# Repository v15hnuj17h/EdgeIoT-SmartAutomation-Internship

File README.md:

# EdgeIoT & Smart Automation Internship

This repository contains my work, notes, code, and documentation from the **10-day EdgeIoT & Smart Automation Internship** conducted by **USIZO Academy**.

Throughout the internship, I explored topics ranging from Git and web deployment to Machine Learning, ESP32 programming, IoT, PCB design, Firebase, and TinyML using Edge Impulse.

---

## Internship Timeline

| Day | Topic | Highlights |
|-----|------|------------|
| **Day 1** | Git & GitHub | Repository creation, version control, documentation using Markdown |
| **Day 2** | Portfolio & Firebase | Built a portfolio website and deployed it using Firebase Hosting |
| **Day 3** | Machine Learning Basics | Introduction to AI, ML pipeline, supervised, unsupervised and reinforcement learning |
| **Day 4** | Development Environment | Installed PlatformIO, ESP32 drivers, Java JDK and required runtimes |
| **Day 5** | Applied Machine Learning | Built a Decision Tree classifier for loan approval prediction using Google Colab |
| **Day 6** | ESP32 Fundamentals | ESP32 architecture, PlatformIO projects, GPIO, Serial communication and PWM |
| **Day 7** | Advanced ESP32 Programming | FreeRTOS, multitasking, timers, GPIO registers, relay control and concurrency |
| **Day 8** | Firebase IoT Dashboard | Controlled an ESP32 remotely using Firebase Realtime Database and a hosted web dashboard |
| **Day 9** | KiCad PCB Design | Designed schematics, PCB layouts, footprints and generated Gerber files |
| **Day 10** | Edge AI & TinyML | Collected MPU6050 motion data, trained an Edge Impulse model and deployed real-time inference on ESP32 |

---

## Repository Structure

```text
.
├── Day-01
├── Day-02
├── Day-03
├── Day-04
├── Day-05
├── Day-06
├── Day-07
├── Day-08
├── Day-09
└── Day-10
```

Each day's folder typically contains:

- `README.md` – Overview of the day's activities
- `notes.md` – Detailed learning notes
- `screenshots/` – Images from practical sessions
- Source code and project files (where applicable)

---

## Technologies & Tools

### Programming
- C++
- Python
- HTML
- CSS
- JavaScript

### Embedded Systems
- ESP32
- MPU6050
- PlatformIO
- Arduino Framework
- FreeRTOS

### IoT & Cloud
- Firebase Hosting
- Firebase Realtime Database

### Machine Learning
- Google Colab
- Scikit-learn
- Decision Trees
- Edge Impulse
- TinyML

### PCB Design
- KiCad

### Version Control
- Git
- GitHub

---

## Skills Gained

- Git and GitHub workflow
- Documentation with Markdown
- Firebase deployment
- Machine Learning fundamentals
- Decision Tree implementation
- ESP32 programming using PlatformIO
- GPIO, PWM and Serial communication
- FreeRTOS multitasking
- Firebase-based IoT applications
- PCB design using KiCad
- Sensor data acquisition
- TinyML model training and deployment
- Real-time inference on ESP32

---

## About

This repository serves as a complete record of my internship journey, documenting both theoretical concepts and practical implementations completed during the program.

It reflects my learning process, hands-on experiments, and projects developed over the course of the internship.

---

**Author:** Vishnujith A

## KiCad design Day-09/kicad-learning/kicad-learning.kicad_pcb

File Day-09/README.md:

# Day 9 - KiCad PCB Design

## Date
26 June 2026

## Objective

Learn the complete PCB design workflow using KiCad, from schematic creation to generating manufacturing files.

## Topics Covered

- Introduction to KiCad
- Schematic Design
- Symbol Libraries
- Footprints
- PCB Layout
- Routing
- Fill Zones
- Silkscreen
- 3D Viewer
- Gerber File Generation

## Activities Performed

- Created a new KiCad project.
- Designed the circuit schematic.
- Assigned footprints to all components.
- Imported the schematic into PCB Editor.
- Placed and routed components.
- Added copper fill zones (Ground Plane).
- Used the silkscreen layer to print text on the PCB.
- Verified the PCB using design rule checks.
- Generated Gerber files.
- Compressed the Gerber files into a ZIP for PCB manufacturing.

## Learning Outcomes

- Learned the complete PCB design workflow.
- Understood the importance of footprints and routing.
- Learned how copper zones improve PCB performance.
- Generated manufacturing-ready Gerber files.

## Summary

Today's session focused on designing a PCB from scratch using KiCad. I completed the full workflow, including schematic design, PCB layout, routing, silkscreen editing, and generating Gerber files for fabrication.

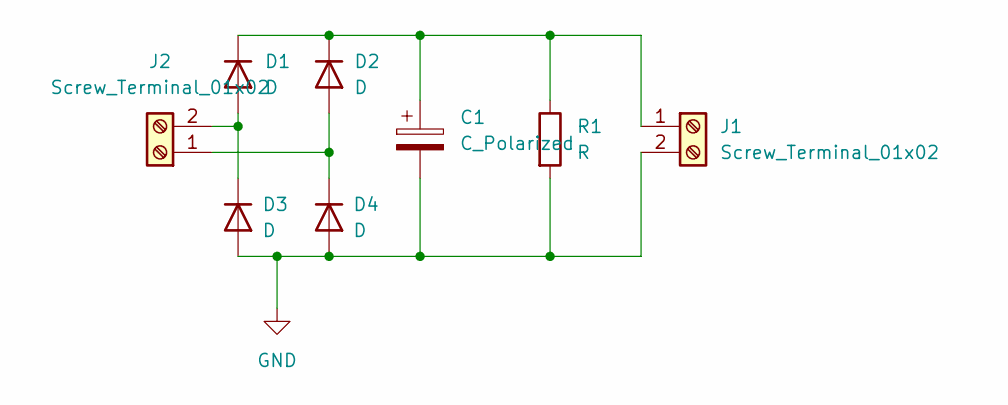
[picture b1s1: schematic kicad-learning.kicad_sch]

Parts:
C1: C_Polarized; CP_Radial_D8.0mm_P5.00mm
D1, D2, D3, D4: D; D_MELF-RM10_Universal_Handsoldering
J1, J2: Screw_Terminal_01x02; TerminalBlock_4Ucon_1x02_P3.50mm_Horizontal
R1: R; R_Axial_DIN0207_L6.3mm_D2.5mm_P7.62mm_Horizontal

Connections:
GND: C1.2, D3.2 (A), D4.2 (A), J1.2, R1.2
unnamed: D1.2 (A), D3.1 (K), J2.2
unnamed: C1.1, D1.1 (K), D2.1 (K), J1.1, R1.1
unnamed: D2.2 (A), D4.1 (K), J2.1

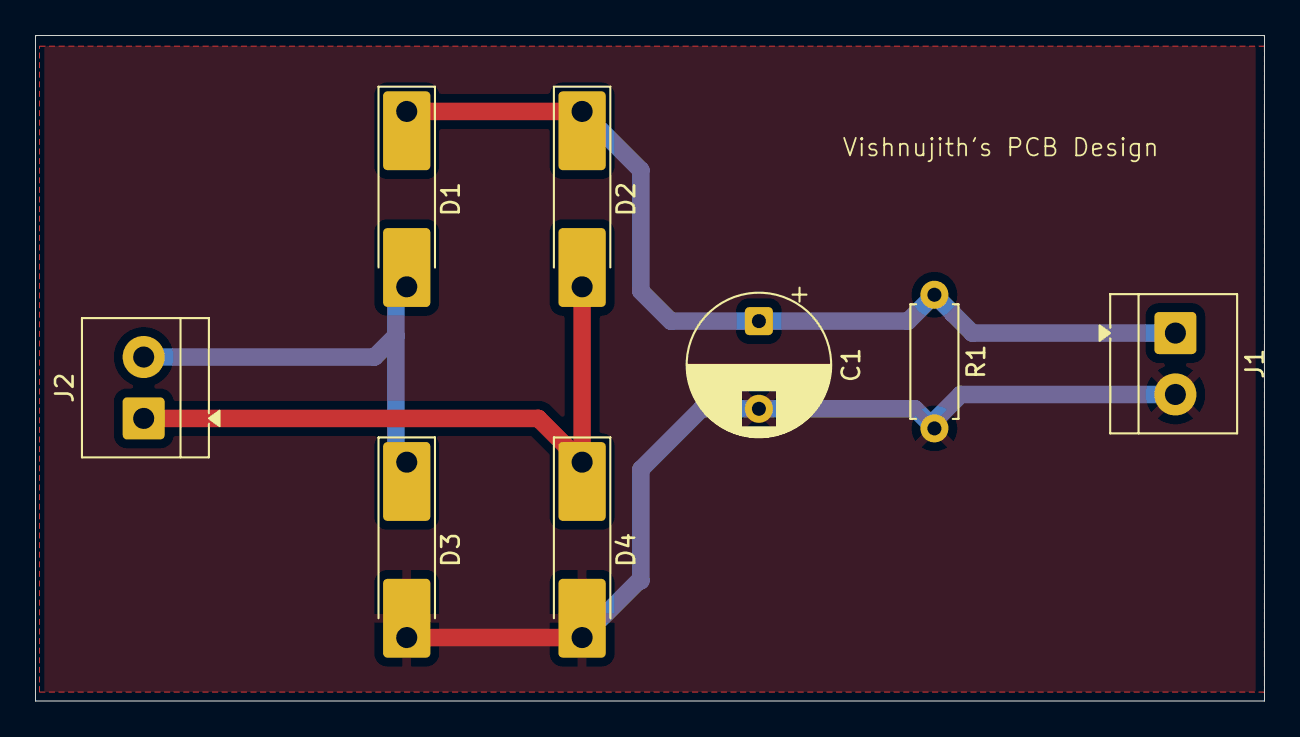
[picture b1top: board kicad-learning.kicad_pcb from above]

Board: 2 copper layers, 70.1 x 37.9 mm, 8 parts (0 on the bottom side), 4 nets.

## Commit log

2026-06-18 Day 1 Done
2026-06-18 Day 1: Git and GitHub
2026-06-19 Day 2: Portfolio Creation and Firebase Deployment
2026-06-20 Day 3: Introduction to ML
2026-06-22 Day 4: Installation & Day 5: Applied ML
2026-06-23 Day 6: Introduction to embedded system
2026-06-24 Day 7: RTOS, LocalHost, etc.
2026-06-26 Day 8: IoT
2026-06-27 Day 9: Kicad
2026-06-27 Day 10: TinyML
